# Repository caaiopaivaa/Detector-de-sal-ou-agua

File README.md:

# Detector-de-sal-ou-gua
Circuito eletrônico micro controlado capaz de detectar presença de sal ou água em solução aquosa.

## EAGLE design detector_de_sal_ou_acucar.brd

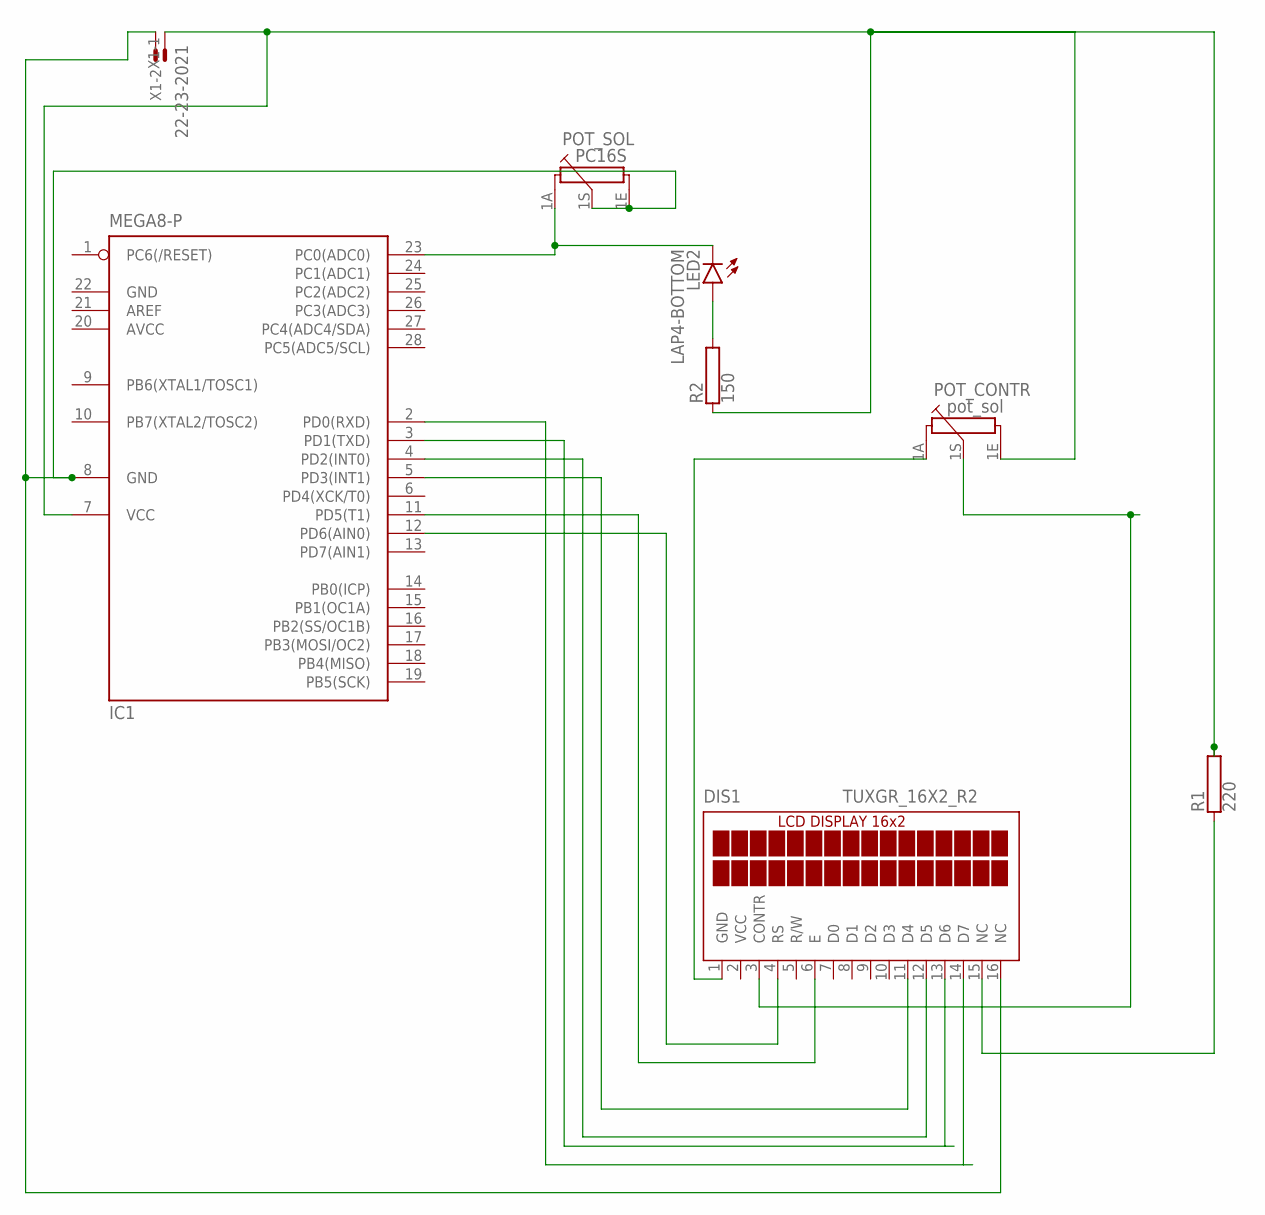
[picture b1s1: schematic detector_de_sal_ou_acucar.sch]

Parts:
DIS1: TUXGR_16X2_R2
IC1: MEGA8-P; DIL28-3
LED2: LAP4-BOTTOM; P47F-BOTTOM
POT_CONTR: pot_sol; PC16S
POT_SOL: PC16S
R1: 220; AC01
R2: 150; AC01
X1: 22-23-2021

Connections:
AVCC: IC1.20 (AVCC)
GND: IC1.22 (GND)
unnamed: DIS1.4 (RS), IC1.12 (PD6(AIN0))
unnamed: DIS1.6 (E), IC1.11 (PD5(T1))
unnamed: DIS1.11 (D4), IC1.5 (PD3(INT1))
unnamed: DIS1.12 (D5), IC1.4 (PD2(INT0))
unnamed: DIS1.13 (D6), IC1.3 (PD1(TXD))
unnamed: DIS1.14 (D7), IC1.2 (PD0(RXD))
unnamed: DIS1.15 (NC), R1.1
unnamed: IC1.7 (VCC), POT_CONTR.1E, R1.2, R2.1, X1.1
unnamed: DIS1.3 (CONTR), POT_CONTR.1S
unnamed: DIS1.1 (GND), POT_CONTR.1A
unnamed: IC1.23 (PC0(ADC0)), LED2.C, POT_SOL.1A
unnamed: DIS1.16 (NC), IC1.8 (GND), POT_SOL.1E, POT_SOL.1S, X1.2
unnamed: LED2.A, R2.2
VCC: DIS1.2 (VCC)

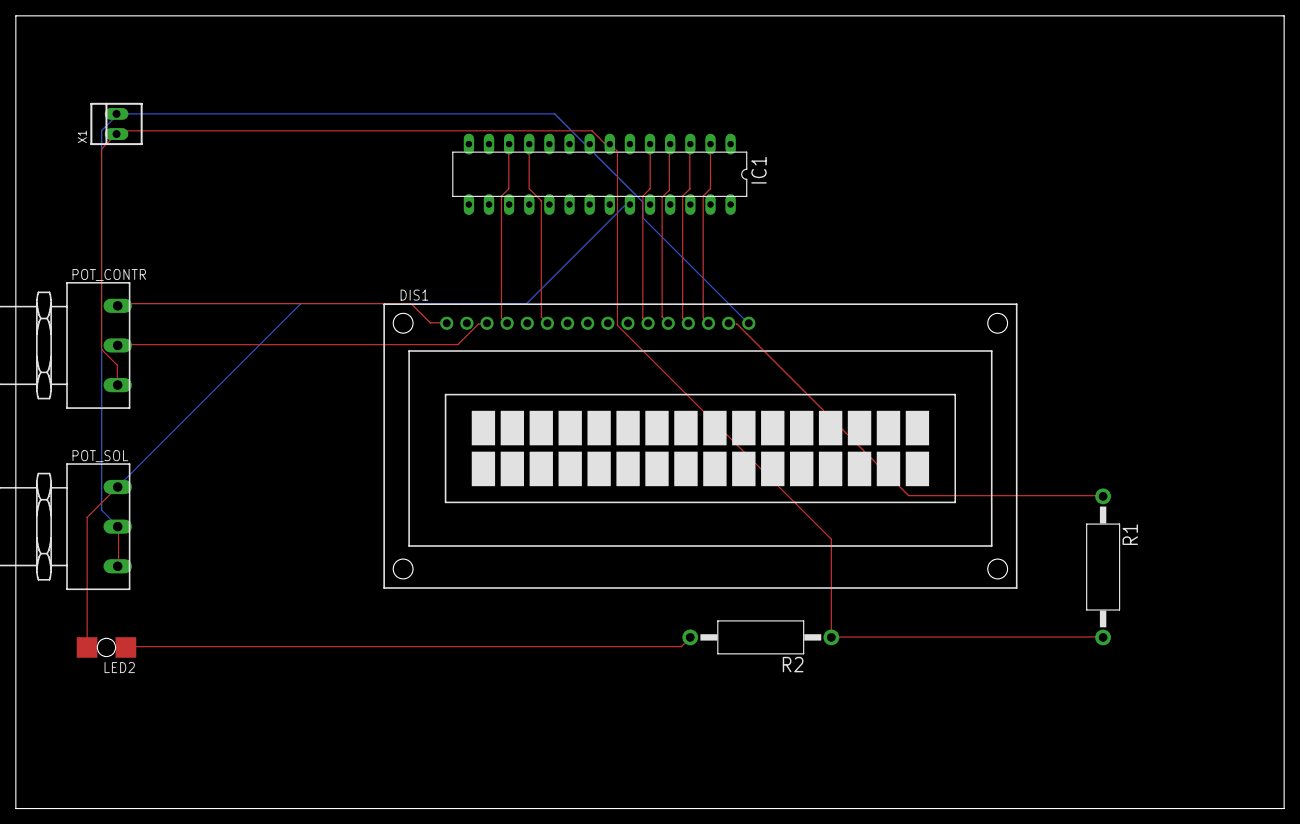
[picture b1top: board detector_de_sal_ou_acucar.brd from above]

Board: 2 copper layers, 160.0 x 100.0 mm, 8 parts (0 on the bottom side), 13 nets.

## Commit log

2020-12-22 Add files via upload
    Imagem gerada no CAD de simulação online tinkercad.
